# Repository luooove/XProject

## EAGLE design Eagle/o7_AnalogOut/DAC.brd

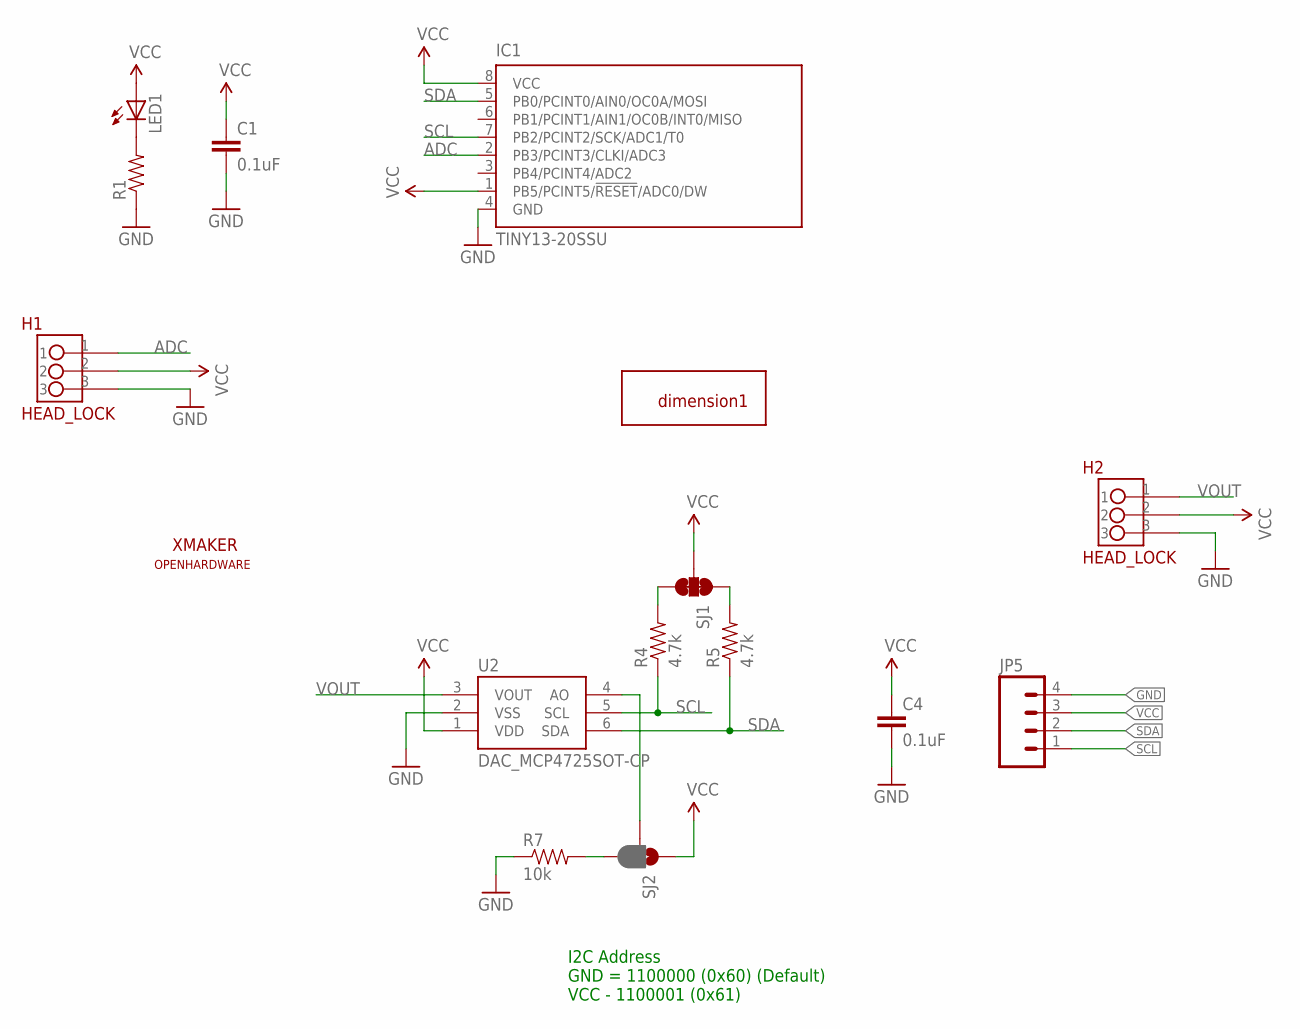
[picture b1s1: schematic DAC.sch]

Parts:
C1, C4: 0.1uF; 0603-CAP
H1, H2: HEAD_LOCK
IC1: TINY13-20SSU; 8S1
JP5: M04PTH; 1X04
LED1: LEDSML0603; SML0603
R1: RESISTOR0603-RES; 0603-RES
R4, R5: 4.7k; 0603-RES
R7: 10k; 0603-RES
SJ1: JUMPER-PAD-3-NC_BY_TRACE; PAD-JUMPER-3-3OF3_NC_BY_TRACE_YES_SILK_FULL_BOX
SJ2: JUMPER-PAD-3-2OF3_NC_BY_PASTE; PAD-JUMPER-3-2OF3_NC_BY_PASTE_YES_SILK_FULL_BOX
U2: DAC_MCP4725SOT-CP; SOT23-6-MCP4725
U$1: XMAKERLOGO2
U$2: DIMENSION1
U$3: OPENHARDWARE

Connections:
ADC: H1.1, IC1.2 (PB3/PCINT3/CLKI/ADC3)
GND: C1.2, C4.2, H1.3, H2.3, IC1.4 (GND), JP5.4, R1.1, R7.1, U2.2 (VSS)
unnamed: LED1.C, R1.2
unnamed: R5.2, SJ1.1
unnamed: R4.2, SJ1.3
unnamed: SJ2.2, U2.4 (AO)
unnamed: R7.2, SJ2.3
SCL: IC1.7 (PB2/PCINT2/SCK/ADC1/T0), JP5.1, R4.1, U2.5 (SCL)
SDA: IC1.5 (PB0/PCINT0/AIN0/OC0A/MOSI), JP5.2, R5.1, U2.6 (SDA)
VCC: C1.1, C4.1, H1.2, H2.2, IC1.1 (PB5/PCINT5/!RESET!/ADC0/DW), IC1.8 (VCC), JP5.3, LED1.A, SJ1.2, SJ2.1, U2.1 (VDD)
VOUT: H2.1, U2.3 (VOUT)

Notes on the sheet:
I2C Address GND = 1100000 (0x60) (Default) VCC - 1100001 (0x61)

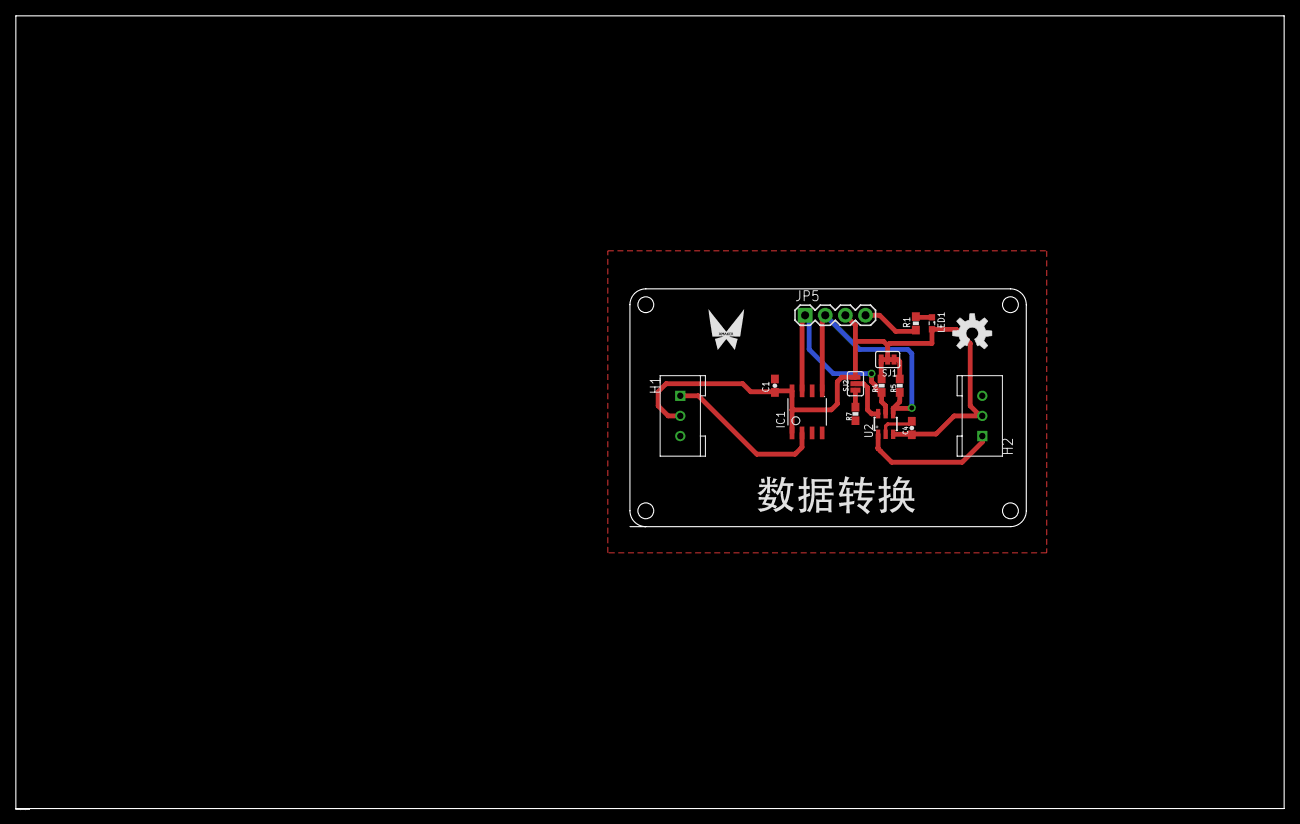
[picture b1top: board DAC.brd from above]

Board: 2 copper layers, 160.0 x 100.0 mm, 17 parts (0 on the bottom side), 11 nets.

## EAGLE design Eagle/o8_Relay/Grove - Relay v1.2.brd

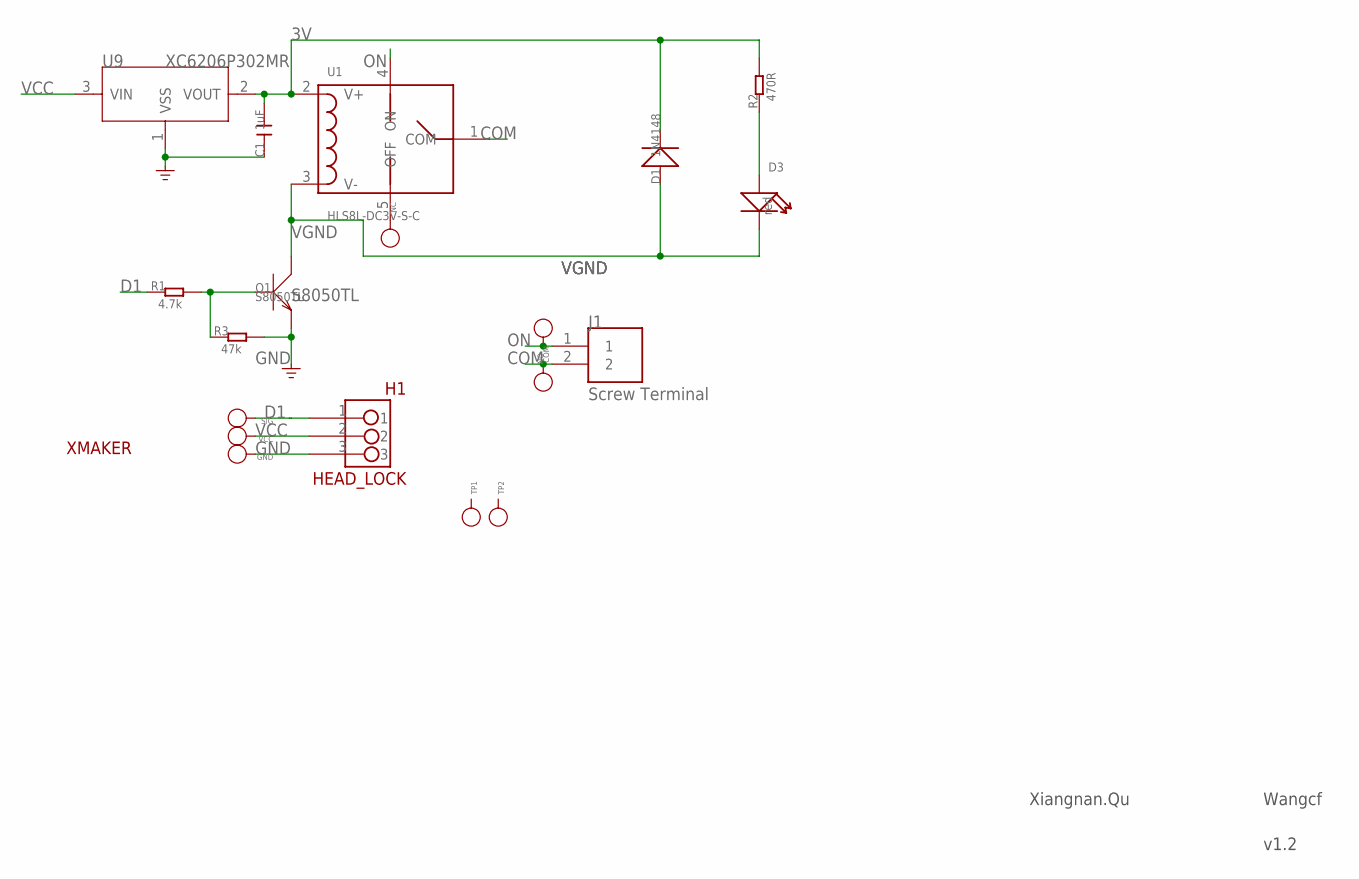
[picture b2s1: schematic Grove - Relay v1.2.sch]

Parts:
C1: 1uF; C0603
COM: PAD-TEST-POINT'4545'; TP_4545
D1: 1N4148; LL-34
D3: red; LED-0603
GND: PAD-TEST-POINT'4545'; TP_4545
H1: HEAD_LOCK
J1: Screw Terminal; CON2
NC: PAD-TEST-POINT'4545'; TP_4545
NO: PAD-TEST-POINT'4545'; TP_4545
Q1: S8050TL; SOT23
R1: 4.7k; R0603
R2: 470R; R0603
R3: 47k; R0603
SIG: PAD-TEST-POINT'4545'; TP_4545
TP1, TP2: PAD-TEST-POINT'4545'; TP_4545
U1: HLS8L-DC3V-S-C; RELAY
U9: XC6206P302MR; SOT23
U$5: XMAKERLOGO2
VCC: PAD-TEST-POINT'4545'; TP_4545

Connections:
3V: C1.2, D1.C (-), R2.2, U1.2 (V+), U9.2 (VOUT)
COM: COM.T, J1.2, U1.1 (COM)
D1: H1.1, R1.1, SIG.T
GND: C1.1, GND.T, H1.3, Q1.2 (E), R3.2, U9.1 (VSS)
unnamed: D3.+, R2.1
unnamed: Q1.1 (B), R1.2, R3.1
unnamed: NC.T, U1.5 (OFF)
ON: J1.1, NO.T, U1.4 (ON)
VCC: H1.2, U9.3 (VIN), VCC.T
VGND: D1.A (+), D3.-, Q1.3 (C), U1.3 (V-)

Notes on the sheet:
S8050TL
Xiangnan.Qu
Wangcf
v1.2

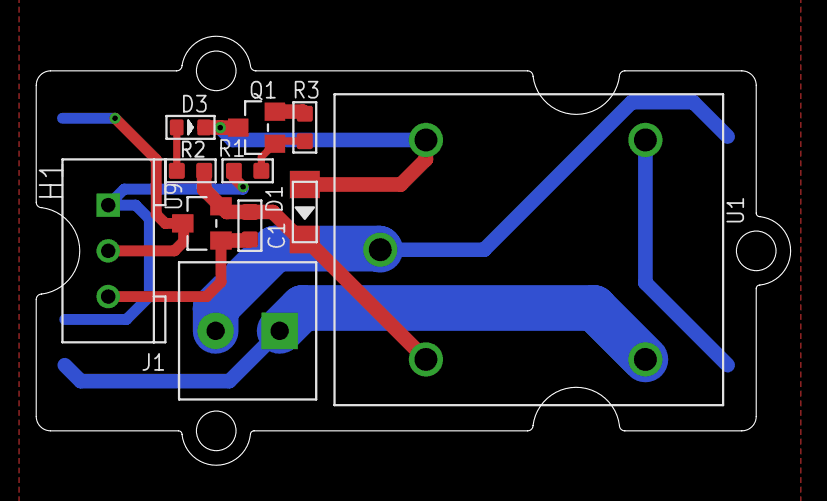
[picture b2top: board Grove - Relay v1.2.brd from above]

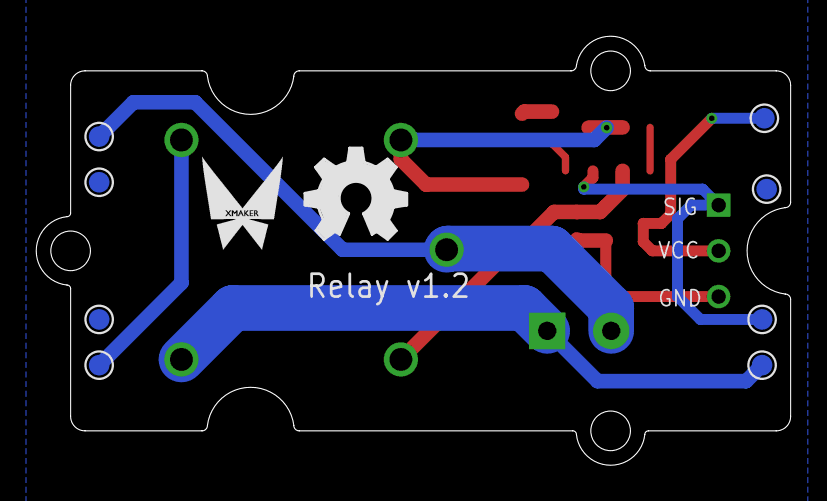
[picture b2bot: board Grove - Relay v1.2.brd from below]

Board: 2 copper layers, 41.9 x 23.8 mm, 22 parts (10 on the bottom side), 10 nets.

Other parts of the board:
U$2: OSHW_FILLX200_NOTEXT
U$3: GROVE-TEST-PLATFORM

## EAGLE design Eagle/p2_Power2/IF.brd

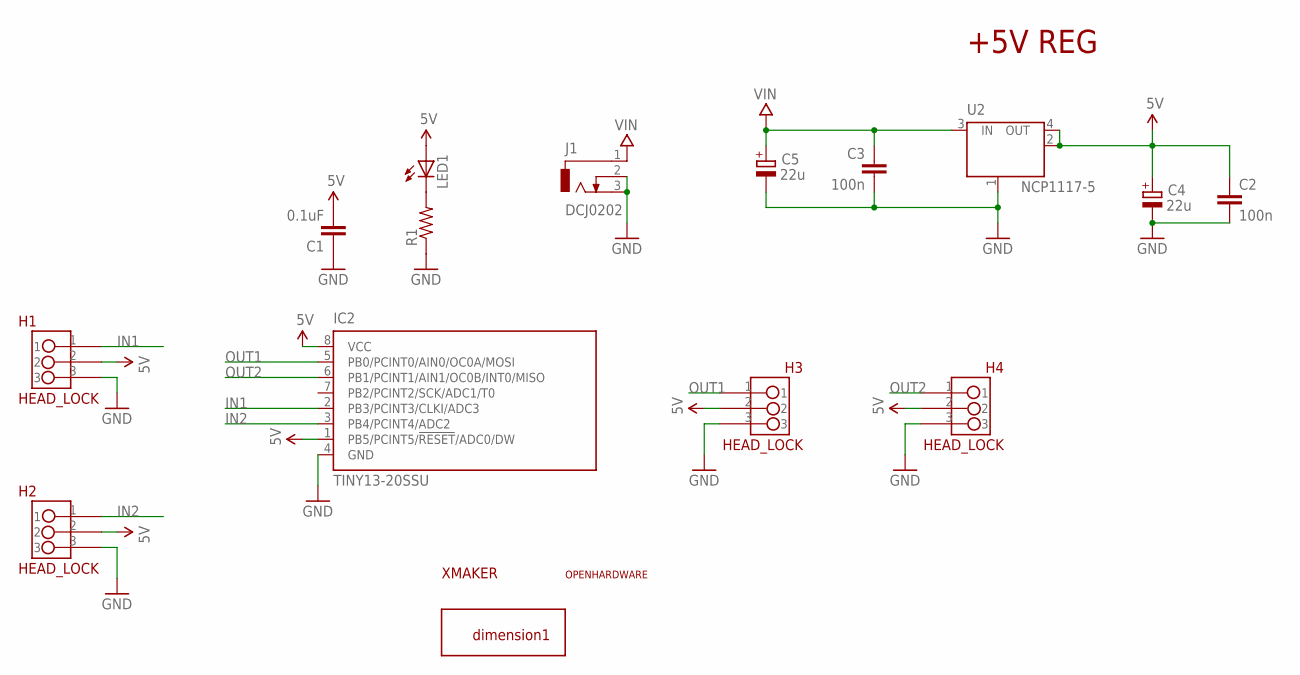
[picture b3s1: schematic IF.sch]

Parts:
C1: 0.1uF; 0603-CAP
C2, C3: 100n; C0402
C4, C5: 22u; SMC_B
H1, H2, H3, H4: HEAD_LOCK
IC2: TINY13-20SSU; 8S1
J1: DCJ0202
LED1: LEDSML0603; SML0603
R1: RESISTOR0603-RES; 0603-RES
U2: NCP1117-5; LINEAR_SOT223
U$2: XMAKERLOGO2
U$3: OPENHARDWARE
U$4: DIMENSION1

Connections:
5V: C1.2, C2.1, C4.+, H1.2, H2.2, H3.2, H4.2, IC2.1 (PB5/PCINT5/!RESET!/ADC0/DW), IC2.8 (VCC), LED1.A, U2.2 (OUT), U2.4 (OUT)
GND: C1.1, C2.2, C3.2, C4.-, C5.-, H1.3, H2.3, H3.3, H4.3, IC2.4 (GND), J1.2, J1.3, R1.1, U2.1 (GND/ADJ)
IN1: H1.1, IC2.2 (PB3/PCINT3/CLKI/ADC3)
IN2: H2.1, IC2.3 (PB4/PCINT4/ADC2)
unnamed: LED1.C, R1.2
OUT1: H3.1, IC2.5 (PB0/PCINT0/AIN0/OC0A/MOSI)
OUT2: H4.1, IC2.6 (PB1/PCINT1/AIN1/OC0B/INT0/MISO)
VIN: C3.1, C5.+, J1.1, U2.3 (IN)

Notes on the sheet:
+5V REG

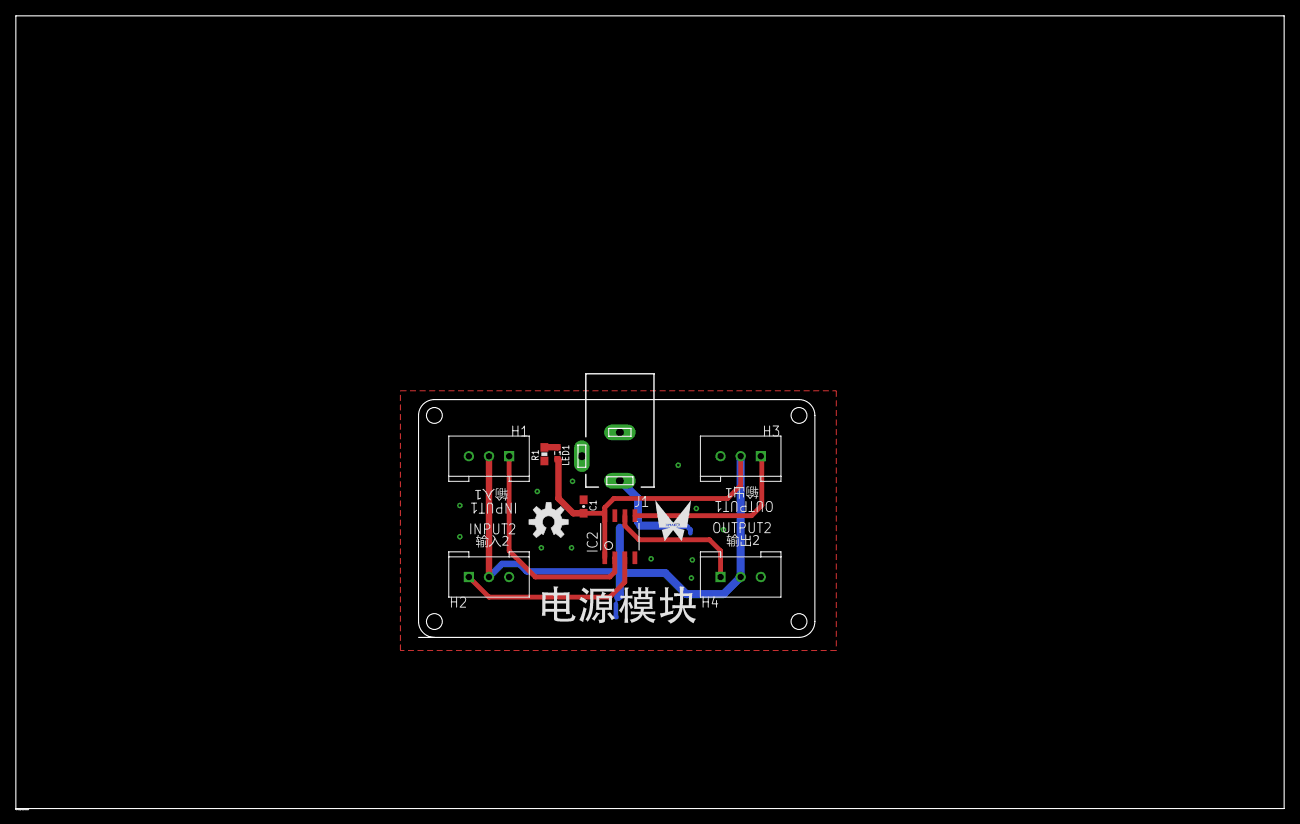
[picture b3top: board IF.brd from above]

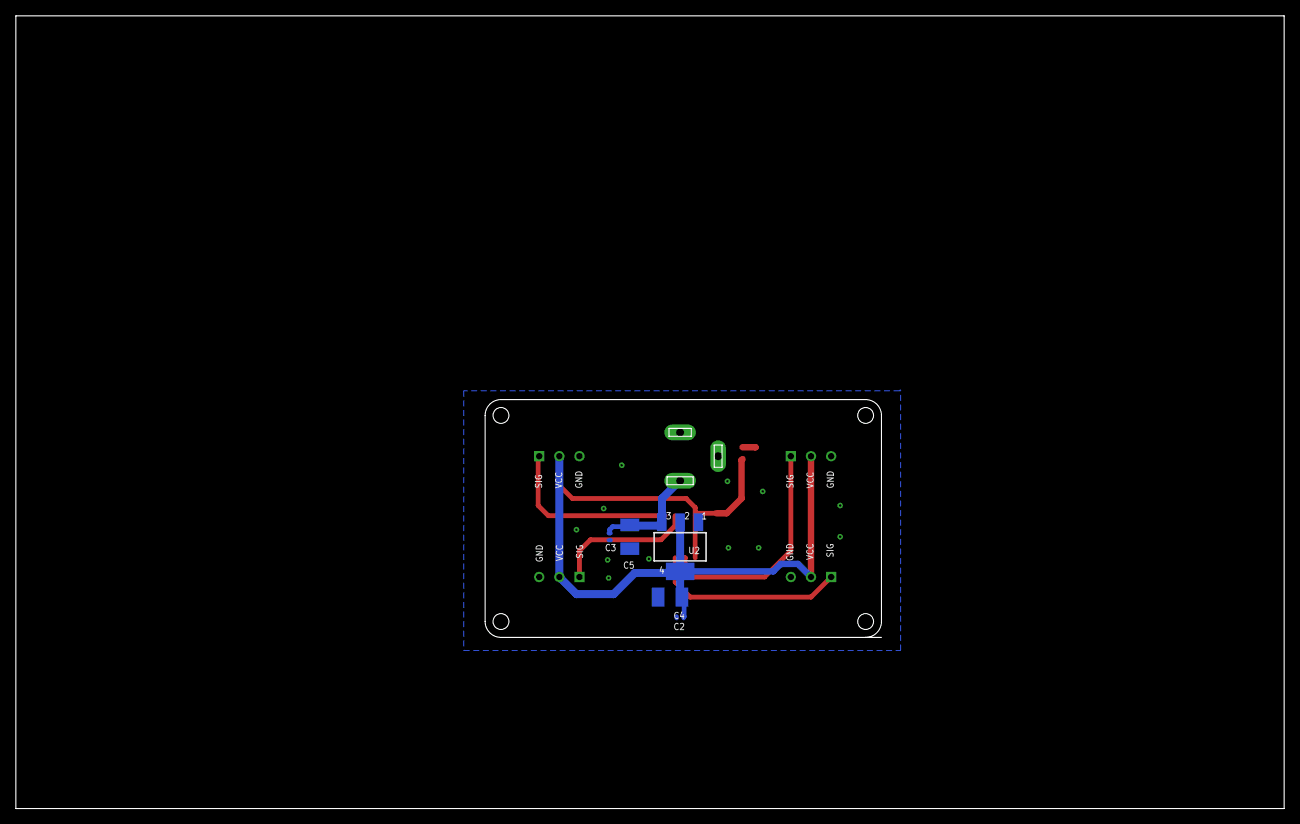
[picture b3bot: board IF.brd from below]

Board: 2 copper layers, 160.0 x 100.0 mm, 17 parts (5 on the bottom side), 8 nets.

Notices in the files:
parts and their libraries:
SparkFun-AnalogIC: Licensing:Creative Commons ShareAlike 4.0 International - https://creativecommons.org/licenses/by-sa/4.0
